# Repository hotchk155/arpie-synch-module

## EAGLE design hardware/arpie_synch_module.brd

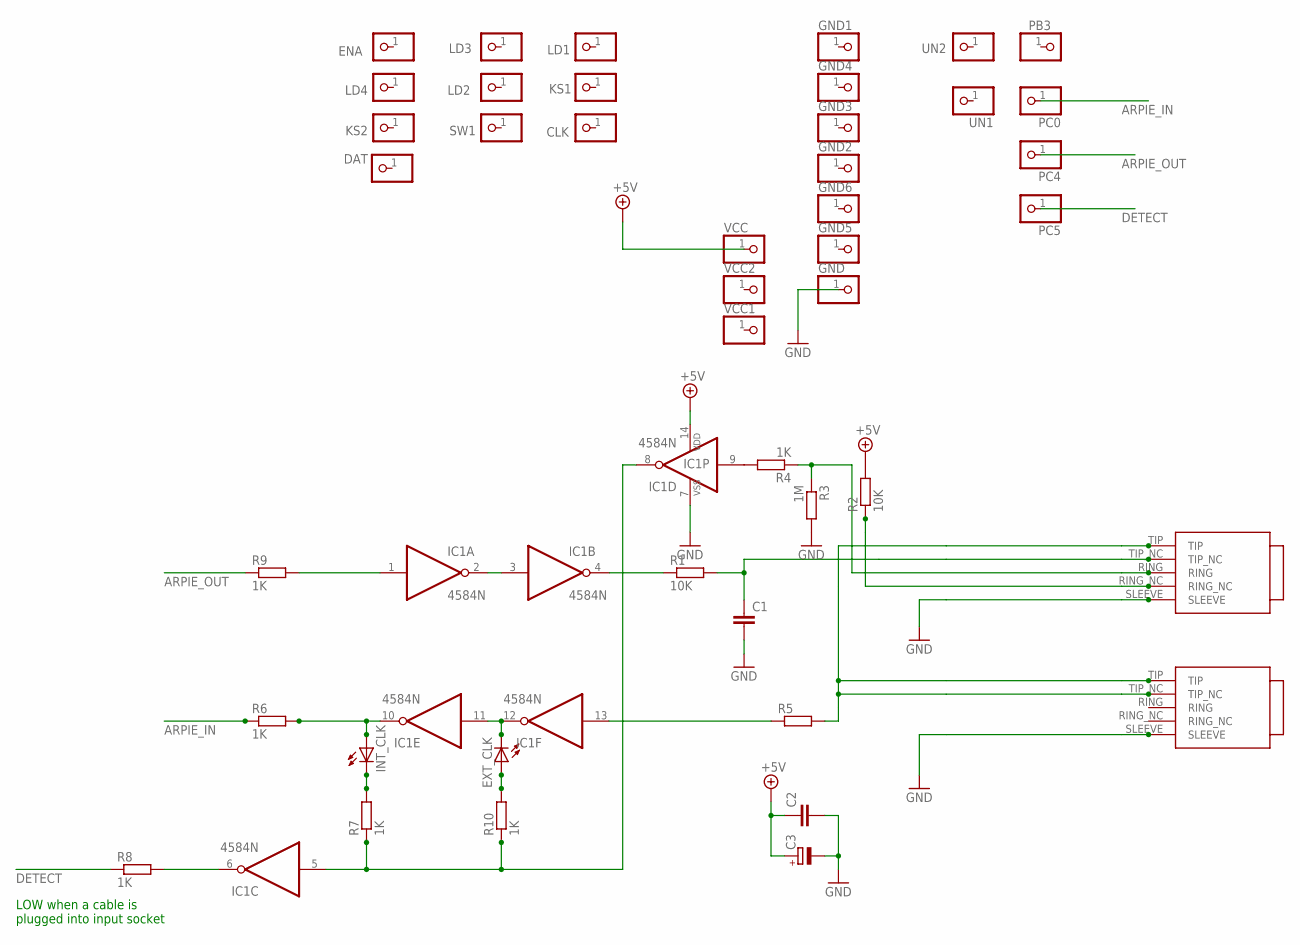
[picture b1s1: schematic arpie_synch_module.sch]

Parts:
C1, C2: C-EU025-030X050; C025-030X050
C3: CPOL-EUE2-5; E2-5
CLK: PINHD-1X1; 1X01
DAT: PINHD-1X1; 1X01
ENA: PINHD-1X1; 1X01
EXT_CLK: LED3MM
GND, GND1, GND2, GND3, GND4, GND5, GND6: PINHD-1X1; 1X01
IC1: 4584N; DIL14
INT_CLK: LED3MM
KS1, KS2: PINHD-1X1; 1X01
LD1, LD2, LD3, LD4: PINHD-1X1; 1X01
PB3: PINHD-1X1; 1X01
PC0, PC4, PC5: PINHD-1X1; 1X01
R1, R2: 10K; 0207/7
R3: 1M; 0207/7
R4, R6, R7, R8, R9, R10: 1K; 0207/7
R5: R-EU_0207/7; 0207/7
SW1: PINHD-1X1; 1X01
U$1, U$2: TRUCONNECTJACK
UN1, UN2: PINHD-1X1; 1X01
VCC, VCC1, VCC2: PINHD-1X1; 1X01

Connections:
+5V: C2.1, C3.+, IC1.14 (VDD), R2.2, VCC.1
ARPIE_IN: PC0.1, R6.1
ARPIE_OUT: PC4.1, R9.1
DETECT: PC5.1, R8.1
GND: C1.2, C2.2, C3.-, GND.1, IC1.7 (VSS), R3.2, U$1.SLEEVE, U$2.SLEEVE
unnamed: IC1.5 (I), IC1.8 (O), R7.1, R10.1
unnamed: R5.2, U$1.TIP, U$2.TIP, U$2.TIP_NC
unnamed: C1.1, R1.2, U$1.TIP_NC
unnamed: IC1.4 (O), R1.1
unnamed: IC1.2 (O), IC1.3 (I)
unnamed: IC1.1 (I), R9.2
unnamed: R2.1, U$1.RING_NC
unnamed: INT_CLK.K (C), R7.2
unnamed: R3.1, R4.1, U$1.RING
unnamed: IC1.9 (I), R4.2
unnamed: IC1.6 (O), R8.2
unnamed: EXT_CLK.K (C), IC1.11 (I), IC1.12 (O)
unnamed: IC1.13 (I), R5.1
unnamed: IC1.10 (O), INT_CLK.A, R6.2
unnamed: EXT_CLK.A, R10.2

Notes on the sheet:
LOW when a cable is plugged into input socket

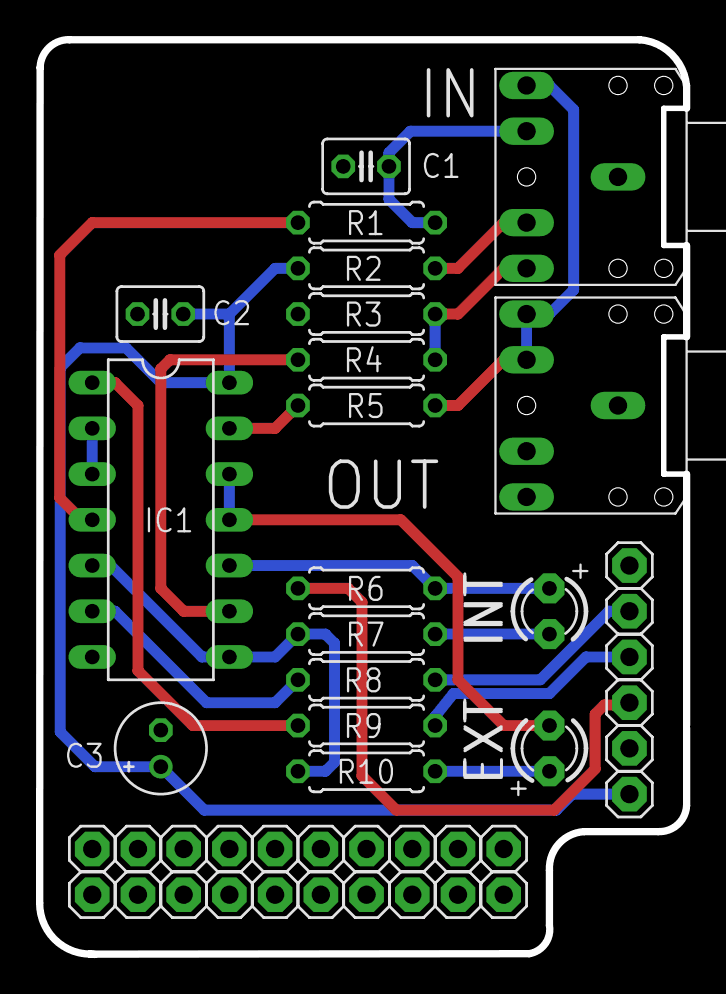
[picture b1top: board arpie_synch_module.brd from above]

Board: 2 copper layers, 35.9 x 50.8 mm, 44 parts (0 on the bottom side), 20 nets.

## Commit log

2014-11-30 rev2
2015-01-04 rev3
2015-01-06 ready
2015-04-27 rev4
    fix connection issue, add recess for socket barrel
2015-07-04 images
